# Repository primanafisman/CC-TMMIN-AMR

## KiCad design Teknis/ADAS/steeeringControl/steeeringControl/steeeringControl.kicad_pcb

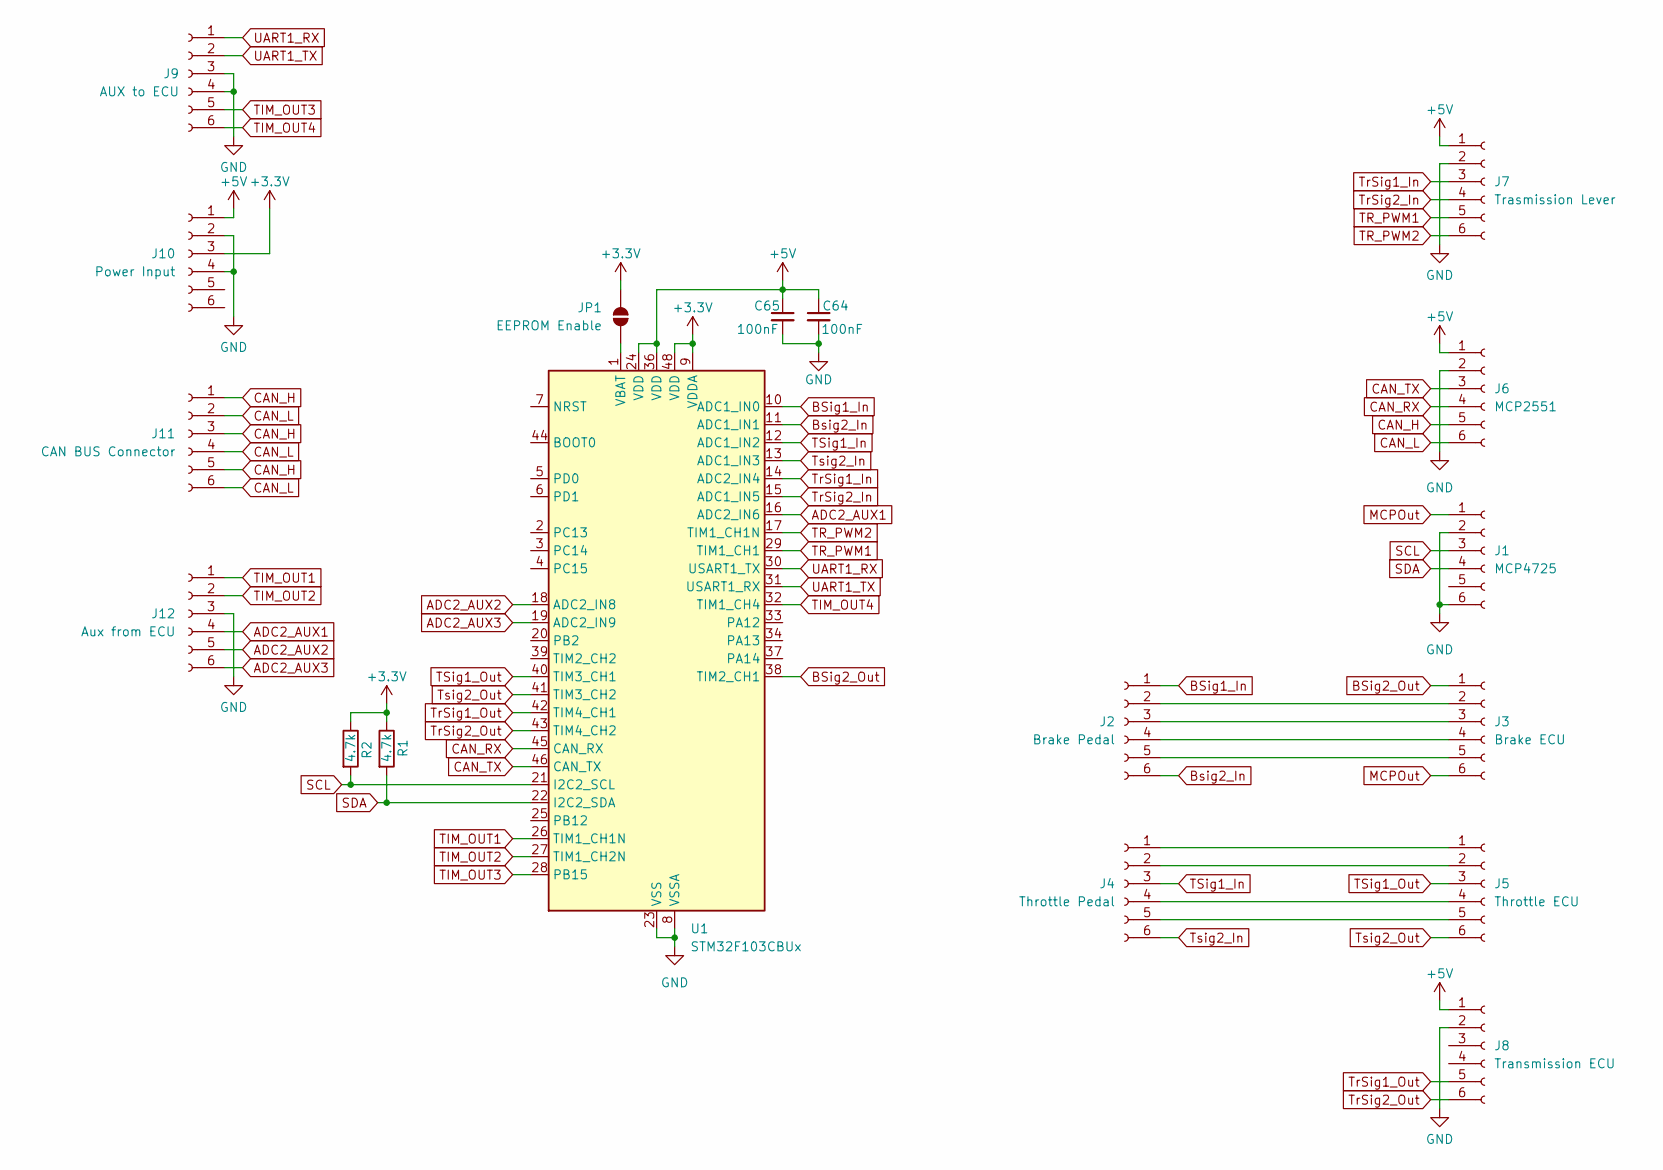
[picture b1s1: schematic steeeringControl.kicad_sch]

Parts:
C64, C65: 100nF; C_0805_2012Metric
J1: MCP4725; PinSocket_1x06_P2.54mm_Vertical
J2: Brake Pedal; JST_XH_S6B-XH-A-1_1x06_P2.50mm_Horizontal
J3: Brake ECU; JST_XH_S6B-XH-A-1_1x06_P2.50mm_Horizontal
J4: Throttle Pedal; JST_XH_S6B-XH-A-1_1x06_P2.50mm_Horizontal
J5: Throttle ECU; JST_XH_S6B-XH-A-1_1x06_P2.50mm_Horizontal
J6: MCP2551; PinSocket_1x06_P2.54mm_Vertical
J7: Trasmission Lever; JST_XH_S6B-XH-A-1_1x06_P2.50mm_Horizontal
J8: Transmission ECU; JST_XH_S6B-XH-A-1_1x06_P2.50mm_Horizontal
J9: AUX to ECU; JST_XH_S6B-XH-A-1_1x06_P2.50mm_Horizontal
J10: Power Input; JST_XH_S6B-XH-A-1_1x06_P2.50mm_Horizontal
J11: CAN BUS Connector; JST_XH_S6B-XH-A-1_1x06_P2.50mm_Horizontal
J12: Aux from ECU; JST_XH_S6B-XH-A-1_1x06_P2.50mm_Horizontal
JP1: EEPROM Enable; SolderJumper-2_P1.3mm_Open_RoundedPad1.0x1.5mm
R1, R2: 4.7k; R_0805_2012Metric
U1: STM32F103CBUx; STM32F103CBT6

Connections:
+3.3V: J10.3, JP1.1 (A), R1.1, R2.1, U1.9 (VDDA), U1.48 (VDD)
+5V: C64.1, C65.1, J6.1, J7.1, J8.1, J10.1, U1.24 (VDD), U1.36 (VDD)
ADC2_AUX1: J12.4, U1.16 (ADC2_IN6)
ADC2_AUX2: J12.5, U1.18 (ADC2_IN8)
ADC2_AUX3: J12.6, U1.19 (ADC2_IN9)
BSig1_In: J2.1, U1.10 (ADC1_IN0)
BSig2_Out: J3.1, U1.38 (TIM2_CH1)
Bsig2_In: J2.6, U1.11 (ADC1_IN1)
CAN_H: J6.5, J11.1, J11.3, J11.5
CAN_L: J6.6, J11.2, J11.4, J11.6
CAN_RX: J6.4, U1.45 (CAN_RX)
CAN_TX: J6.3, U1.46 (CAN_TX)
GND: C64.2, C65.2, J1.2, J1.6, J6.2, J7.2, J8.2, J9.3, J9.4, J10.2, J10.4, J12.3, U1.8 (VSSA), U1.23 (VSS), U1.35 (VSS), U1.47 (VSS), U1.49 (VSS)
MCPOut: J1.1, J3.6
unnamed: J2.2, J3.2
unnamed: J2.3, J3.3
unnamed: J2.4, J3.4
unnamed: J2.5, J3.5
unnamed: J4.1, J5.1
unnamed: J4.2, J5.2
unnamed: J4.4, J5.4
unnamed: J4.5, J5.5
unnamed: JP1.2 (B), U1.1 (VBAT)
SCL: J1.3, R2.2, U1.21 (I2C2_SCL)
SDA: J1.4, R1.2, U1.22 (I2C2_SDA)
TIM_OUT1: J12.1, U1.26 (TIM1_CH1N)
TIM_OUT2: J12.2, U1.27 (TIM1_CH2N)
TIM_OUT3: J9.5, U1.28 (PB15)
TIM_OUT4: J9.6, U1.32 (TIM1_CH4)
TR_PWM1: J7.5, U1.29 (TIM1_CH1)
TR_PWM2: J7.6, U1.17 (TIM1_CH1N)
TSig1_In: J4.3, U1.12 (ADC1_IN2)
TSig1_Out: J5.3, U1.40 (TIM3_CH1)
TrSig1_In: J7.3, U1.14 (ADC2_IN4)
TrSig1_Out: J8.5, U1.42 (TIM4_CH1)
TrSig2_In: J7.4, U1.15 (ADC1_IN5)
TrSig2_Out: J8.6, U1.43 (TIM4_CH2)
Tsig2_In: J4.6, U1.13 (ADC1_IN3)
Tsig2_Out: J5.6, U1.41 (TIM3_CH2)
UART1_RX: J9.1, U1.30 (USART1_TX)
UART1_TX: J9.2, U1.31 (USART1_RX)

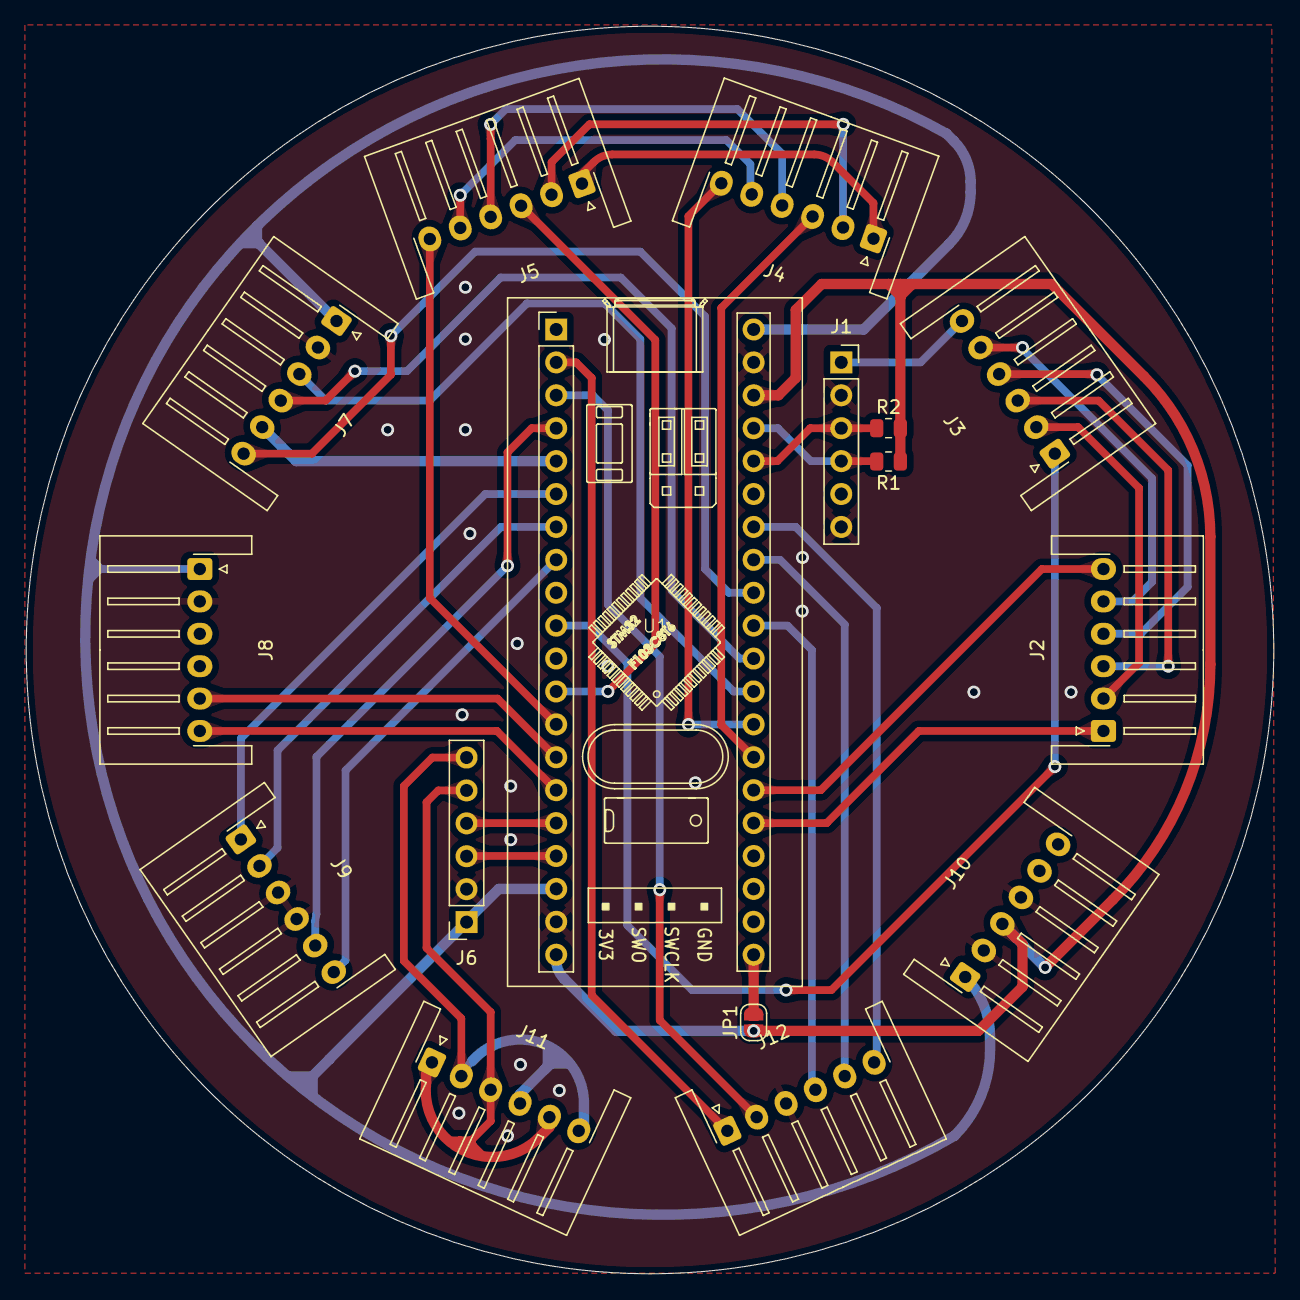
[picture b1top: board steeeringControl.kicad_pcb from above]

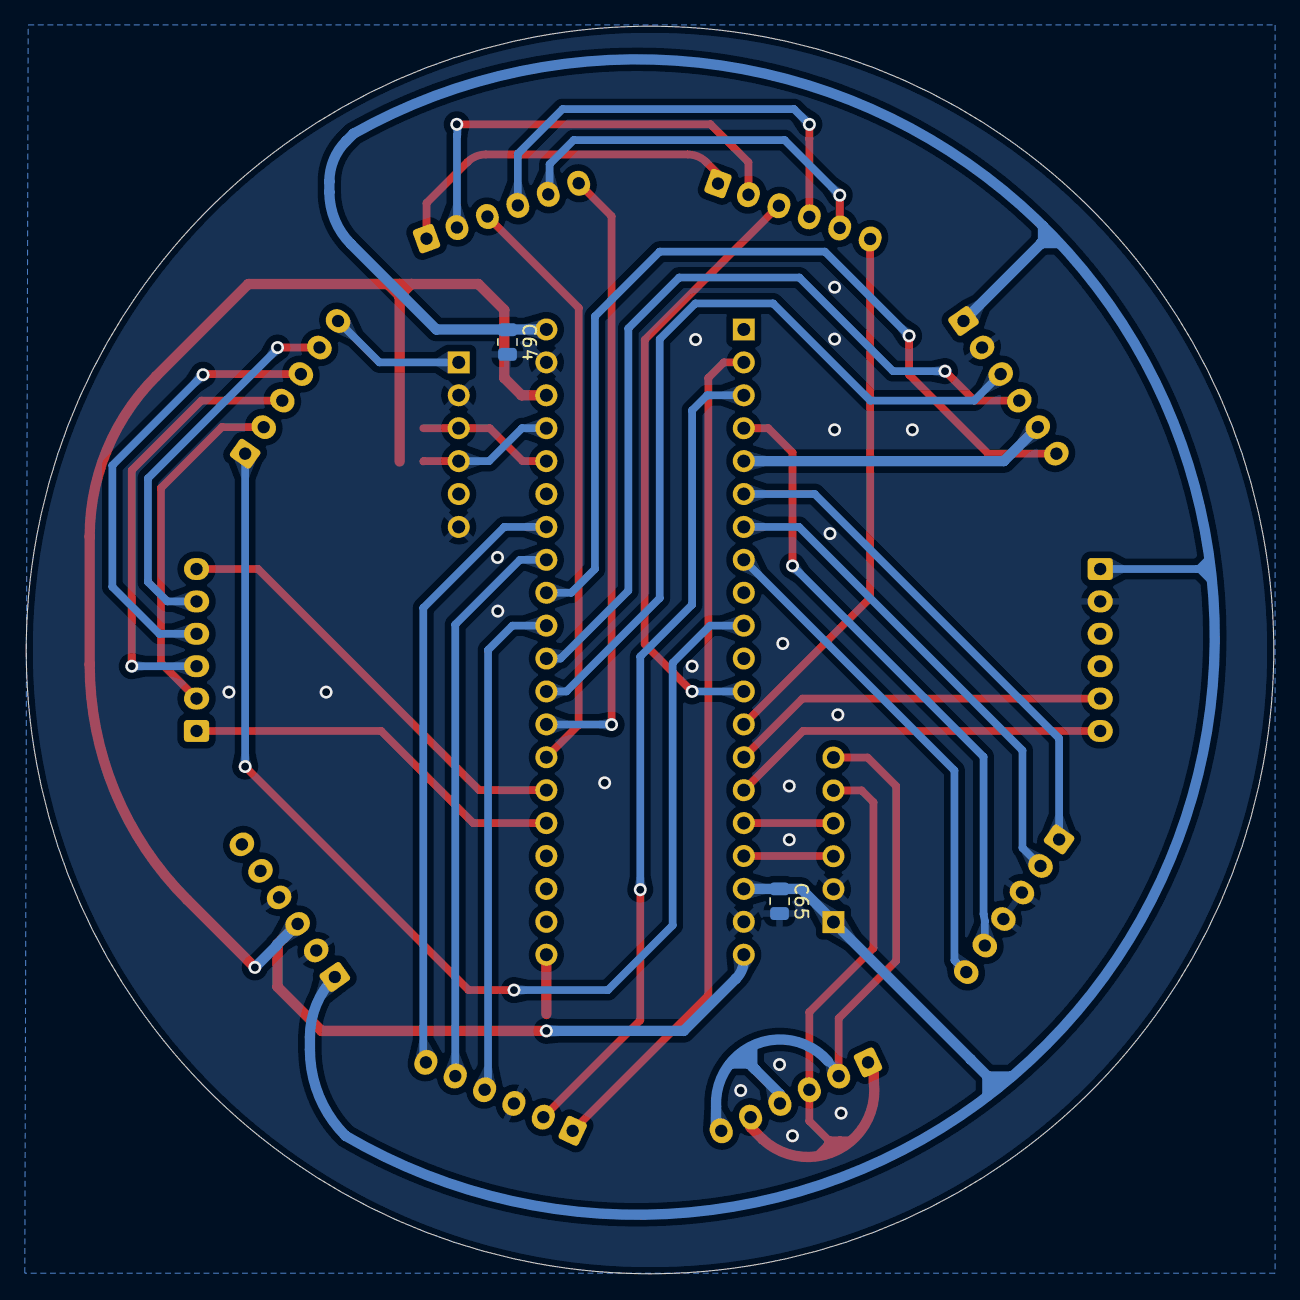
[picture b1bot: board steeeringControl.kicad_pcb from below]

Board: 2 copper layers, 96.3 x 96.3 mm, 18 parts (2 on the bottom side), 41 nets.

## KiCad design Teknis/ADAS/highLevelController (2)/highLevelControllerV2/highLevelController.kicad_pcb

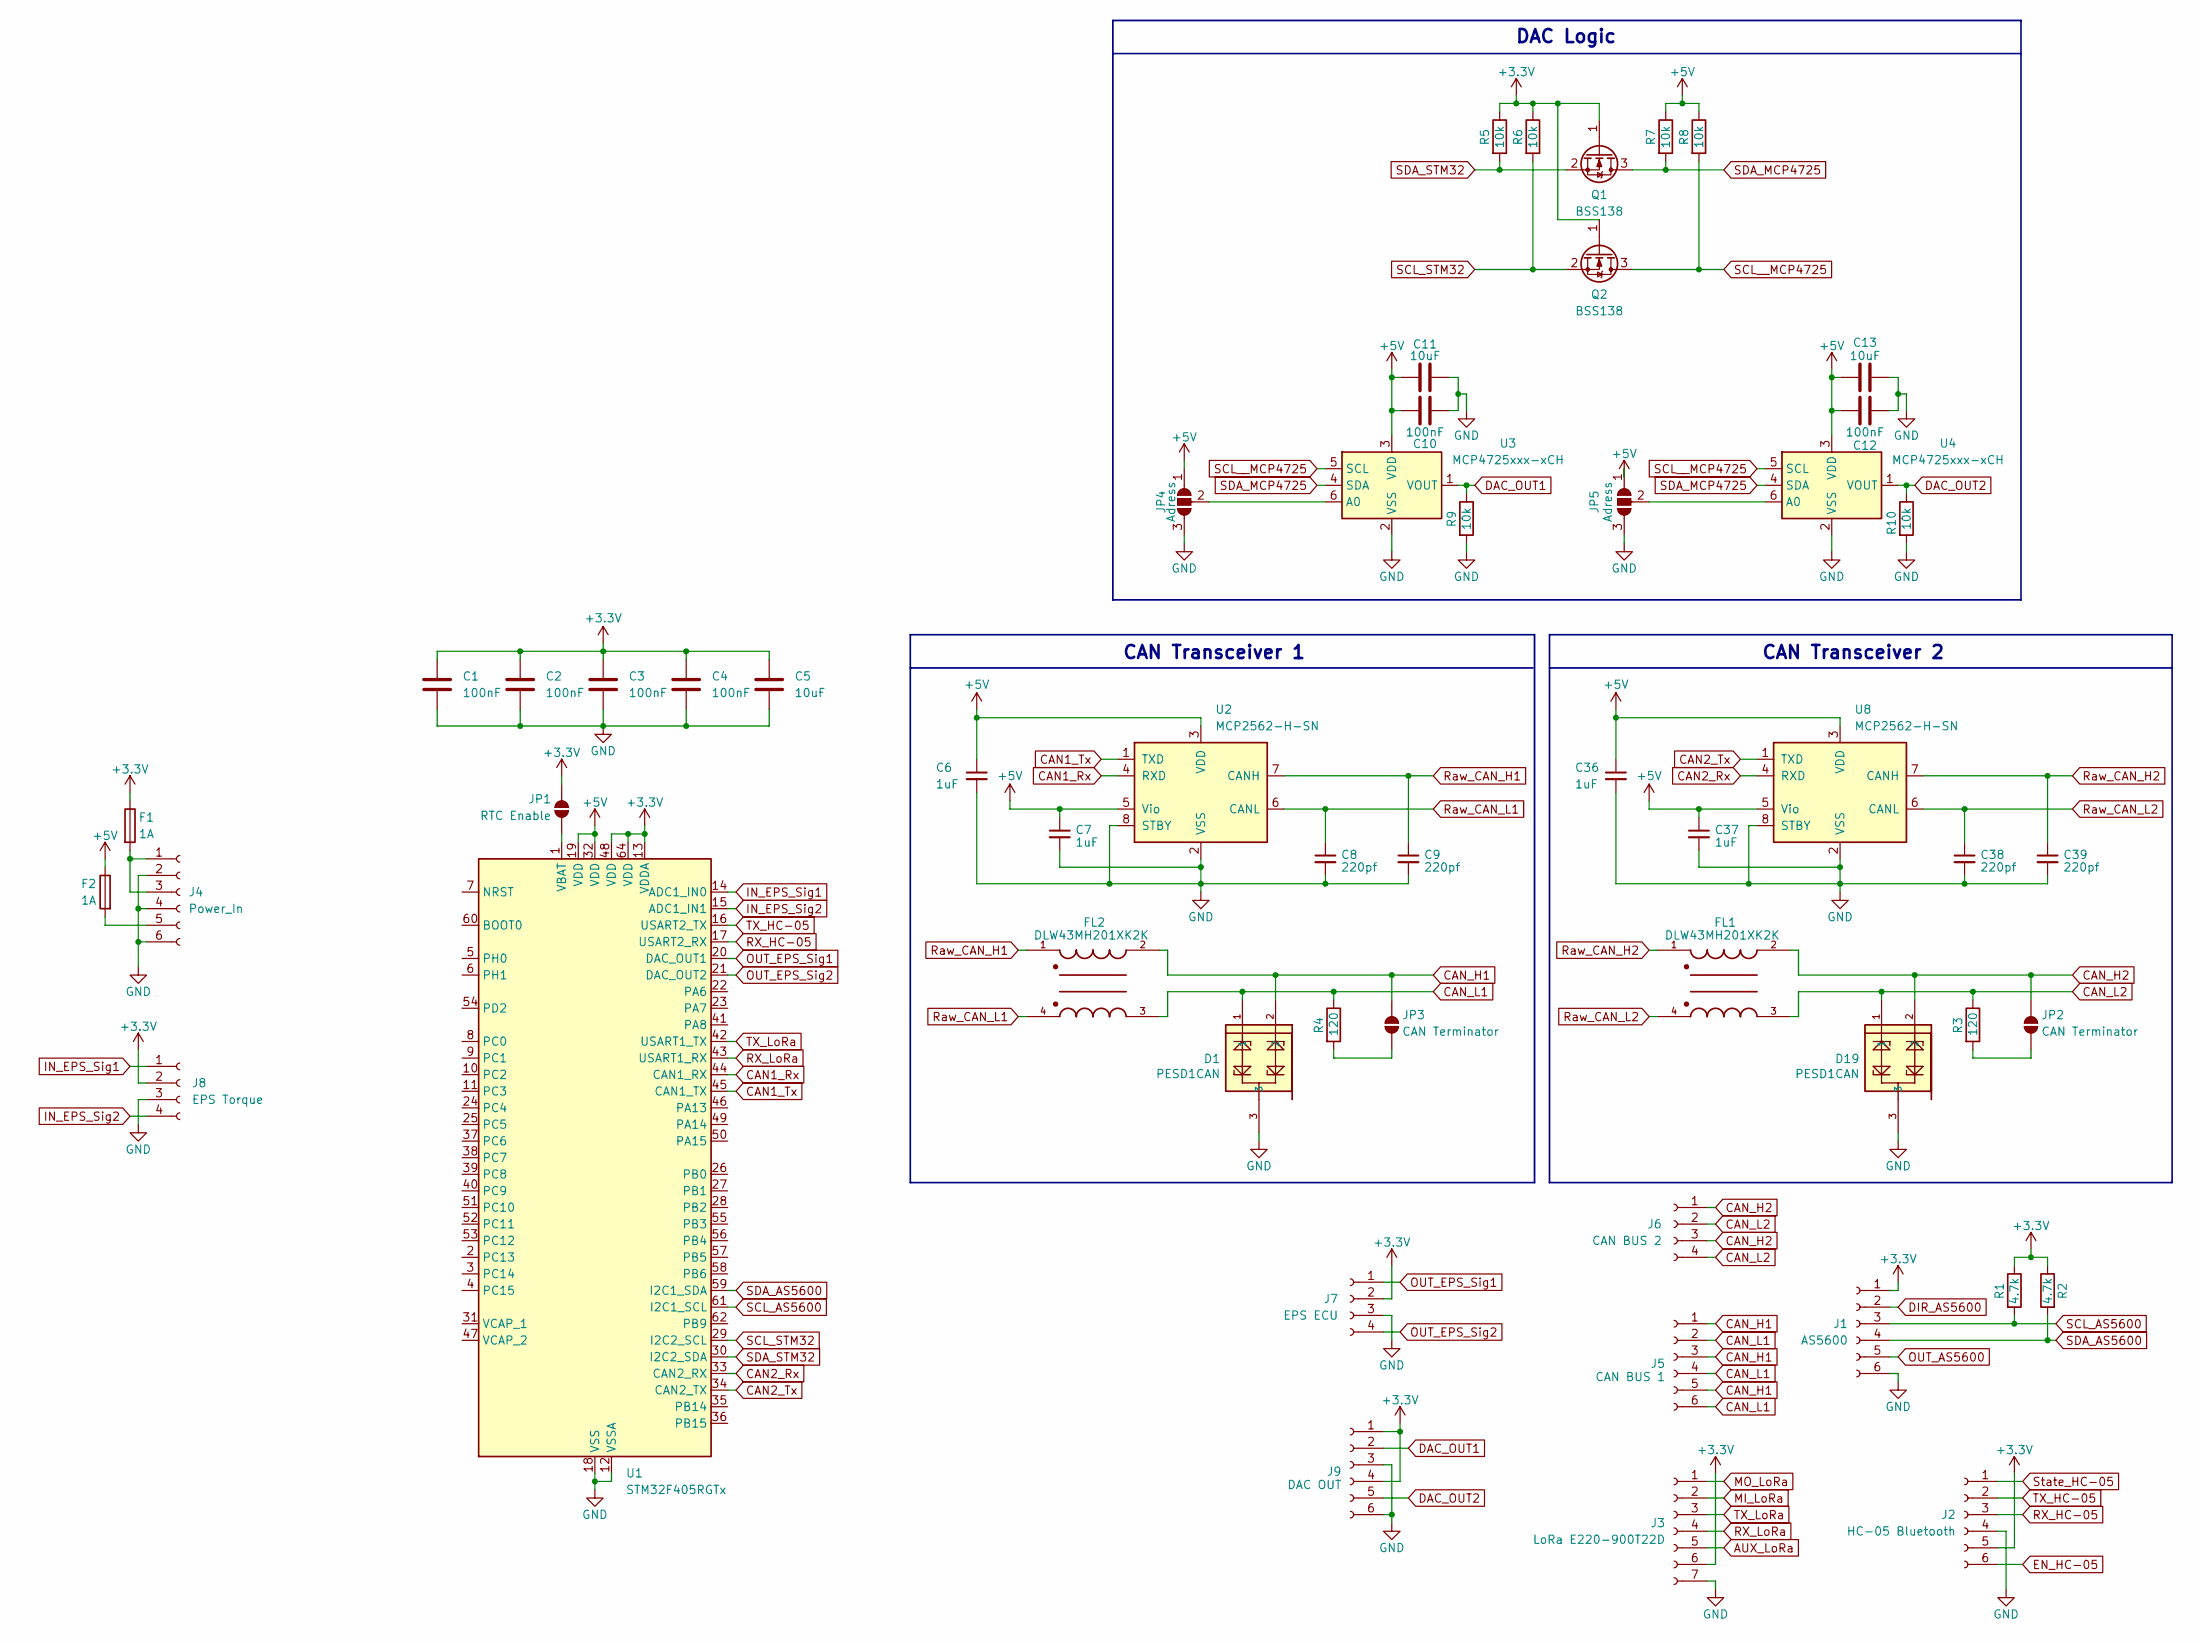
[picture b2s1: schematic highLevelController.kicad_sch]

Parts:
C1, C2, C3, C4, C10, C12: 100nF; C_0603_1608Metric
C5, C11, C13: 10uF; C_0603_1608Metric
C6, C7, C36, C37: 1uF; C_0603_1608Metric
C8, C9, C38, C39: 220pf; C_0603_1608Metric
D1, D19: PESD1CAN; SOT-23
F1, F2: 1A; Fuse_1206_3216Metric
FL1, FL2: DLW43MH201XK2K; DLW43; PARTREV N/A
J1: AS5600; JST_XH_S6B-XH-A-1_1x06_P2.50mm_Horizontal
J2: HC-05 Bluetooth; PinSocket_1x06_P2.54mm_Vertical
J3: LoRa E220-900T22D; PinSocket_1x07_P2.54mm_Vertical
J4: Power_In; JST_XH_S6B-XH-A-1_1x06_P2.50mm_Horizontal
J5: CAN BUS 1; JST_XH_S6B-XH-A-1_1x06_P2.50mm_Horizontal
J6: CAN BUS 2; JST_XH_S4B-XH-A-1_1x04_P2.50mm_Horizontal
J7: EPS ECU; JST_XH_S4B-XH-A-1_1x04_P2.50mm_Horizontal
J8: EPS Torque; JST_XH_S4B-XH-A-1_1x04_P2.50mm_Horizontal
J9: DAC OUT; JST_XH_S6B-XH-A-1_1x06_P2.50mm_Horizontal
JP1: RTC Enable; SolderJumper-2_P1.3mm_Open_TrianglePad1.0x1.5mm
JP2, JP3: CAN Terminator; SolderJumper-2_P1.3mm_Open_TrianglePad1.0x1.5mm
JP4, JP5: Adress; SolderJumper-3_P2.0mm_Open_TrianglePad1.0x1.5mm_NumberLabels
Q1, Q2: BSS138; SOT-23
R1, R2: 4.7k; R_0603_1608Metric
R3, R4: 120; R_0603_1608Metric
R5, R6, R7, R8, R9, R10: 10k; R_0603_1608Metric
U1: STM32F405RGTx; STM32F405RGT6
U2, U8: MCP2562-H-SN; SOIC-8_3.9x4.9mm_P1.27mm
U3, U4: MCP4725xxx-xCH; SOT-23-6

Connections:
+3.3V: C1.1, C2.1, C3.1, C4.1, C5.1, F1.1, J1.1, J2.5, J3.6, J7.2, J8.2, J9.1, J9.4, JP1.1 (A), Q1.1 (G), Q2.1 (G), R1.1, R2.1, R5.1, R6.1, U1.13 (VDDA), U1.48 (VDD), U1.64 (VDD)
+5V: C6.1, C7.1, C10.1, C11.1, C12.1, C13.1, C36.1, C37.1, F2.1, JP4.1 (A), JP5.1 (A), R7.1, R8.1, U1.19 (VDD), U1.32 (VDD), U2.3 (VDD), U2.5 (Vio), U3.3 (VDD), U4.3 (VDD), U8.3 (VDD), U8.5 (Vio)
AUX_LoRa: J3.5
CAN1_Rx: U1.44 (CAN1_RX), U2.4 (RXD)
CAN1_Tx: U1.45 (CAN1_TX), U2.1 (TXD)
CAN2_Rx: U1.33 (CAN2_RX), U8.4 (RXD)
CAN2_Tx: U1.34 (CAN2_TX), U8.1 (TXD)
CAN_H1: D1.2, FL2.2, J5.1, J5.3, J5.5, JP3.1 (A)
CAN_H2: D19.2, FL1.2, J6.1, J6.3, JP2.1 (A)
CAN_L1: D1.1, FL2.3, J5.2, J5.4, J5.6, R4.1
CAN_L2: D19.1, FL1.3, J6.2, J6.4, R3.1
DAC_OUT1: J9.2, R9.1, U3.1 (VOUT)
DAC_OUT2: J9.5, R10.1, U4.1 (VOUT)
DIR_AS5600: J1.2
EN_HC-05: J2.6
GND: C1.2, C2.2, C3.2, C4.2, C5.2, C6.2, C7.2, C8.2, C9.2, C10.2, C11.2, C12.2, C13.2, C36.2, C37.2, C38.2, C39.2, D1.3, D19.3, J1.6, J2.4, J3.7, J4.2, J4.4, J4.6, J7.3, J8.3, J9.3, J9.6, JP4.3 (B), JP5.3 (B), R9.2, R10.2, U1.12 (VSSA), U1.18 (VSS), U1.63 (VSS), U2.2 (VSS), U2.8 (STBY), U3.2 (VSS), U4.2 (VSS), U8.2 (VSS), U8.8 (STBY)
IN_EPS_Sig1: J8.1, U1.14 (ADC1_IN0)
IN_EPS_Sig2: J8.4, U1.15 (ADC1_IN1)
MI_LoRa: J3.2
MO_LoRa: J3.1
unnamed: F1.2, J4.1, J4.3
unnamed: F2.2, J4.5
unnamed: JP1.2 (B), U1.1 (VBAT)
unnamed: JP2.2 (B), R3.2
unnamed: JP3.2 (B), R4.2
unnamed: JP4.2 (C), U3.6 (A0)
unnamed: JP5.2 (C), U4.6 (A0)
OUT_AS5600: J1.5
OUT_EPS_Sig1: J7.1, U1.20 (DAC_OUT1)
OUT_EPS_Sig2: J7.4, U1.21 (DAC_OUT2)
RX_HC-05: J2.3, U1.17 (USART2_RX)
RX_LoRa: J3.4, U1.43 (USART1_RX)
Raw_CAN_H1: C9.1, FL2.1, U2.7 (CANH)
Raw_CAN_H2: C39.1, FL1.1, U8.7 (CANH)
Raw_CAN_L1: C8.1, FL2.4, U2.6 (CANL)
Raw_CAN_L2: C38.1, FL1.4, U8.6 (CANL)
SCL_AS5600: J1.3, R1.2, U1.61 (I2C1_SCL)
SCL_STM32: Q2.2 (S), R6.2, U1.29 (I2C2_SCL)
SCL__MCP4725: Q2.3 (D), R8.2, U3.5 (SCL), U4.5 (SCL)
SDA_AS5600: J1.4, R2.2, U1.59 (I2C1_SDA)
SDA_MCP4725: Q1.3 (D), R7.2, U3.4 (SDA), U4.4 (SDA)
SDA_STM32: Q1.2 (S), R5.2, U1.30 (I2C2_SDA)
State_HC-05: J2.1
TX_HC-05: J2.2, U1.16 (USART2_TX)
TX_LoRa: J3.3, U1.42 (USART1_TX)

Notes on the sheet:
CAN Transceiver 1
CAN Transceiver 2
DAC Logic

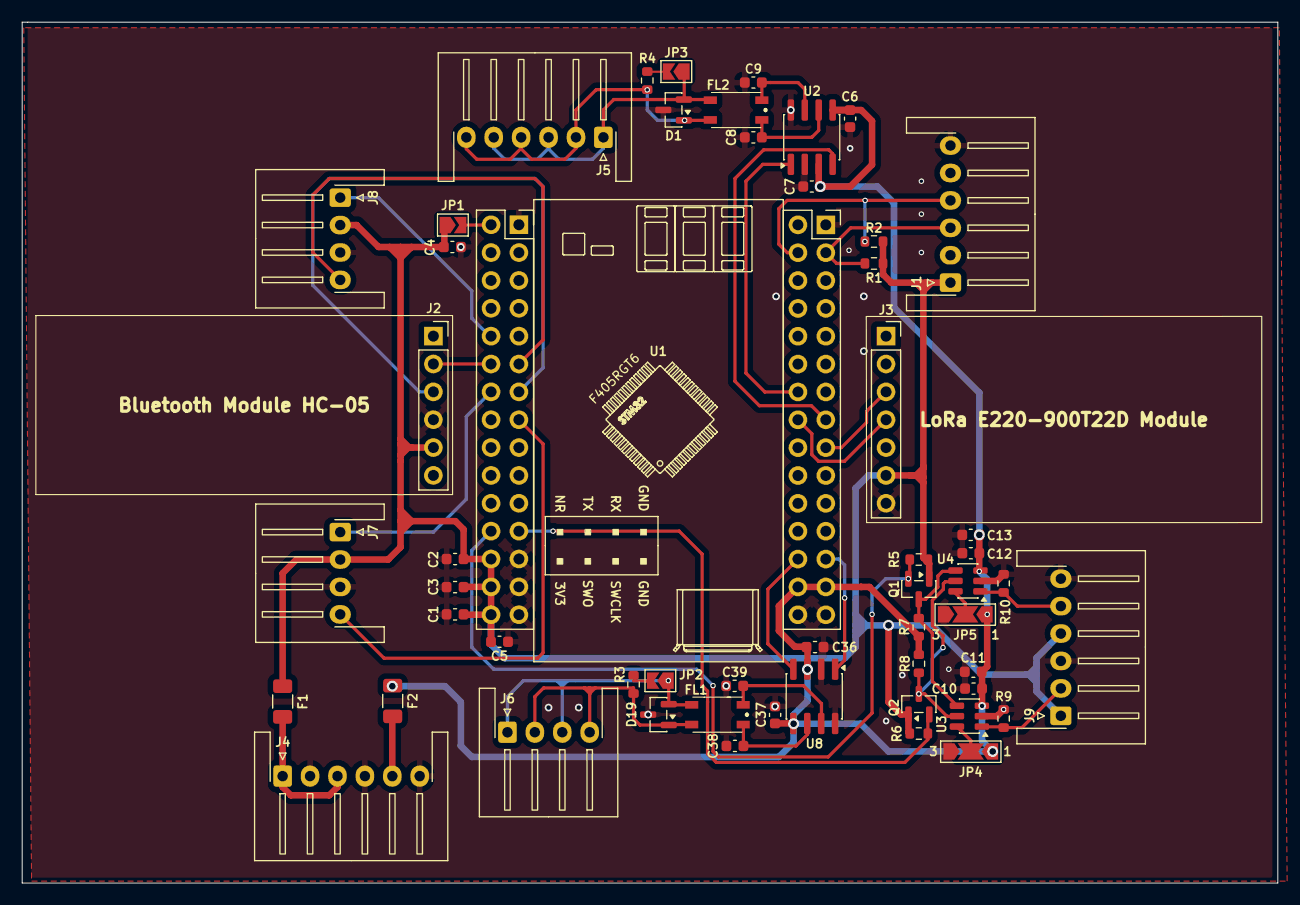
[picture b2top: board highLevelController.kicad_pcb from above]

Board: 2 copper layers, 114.5 x 78.5 mm, 54 parts (0 on the bottom side), 38 nets.

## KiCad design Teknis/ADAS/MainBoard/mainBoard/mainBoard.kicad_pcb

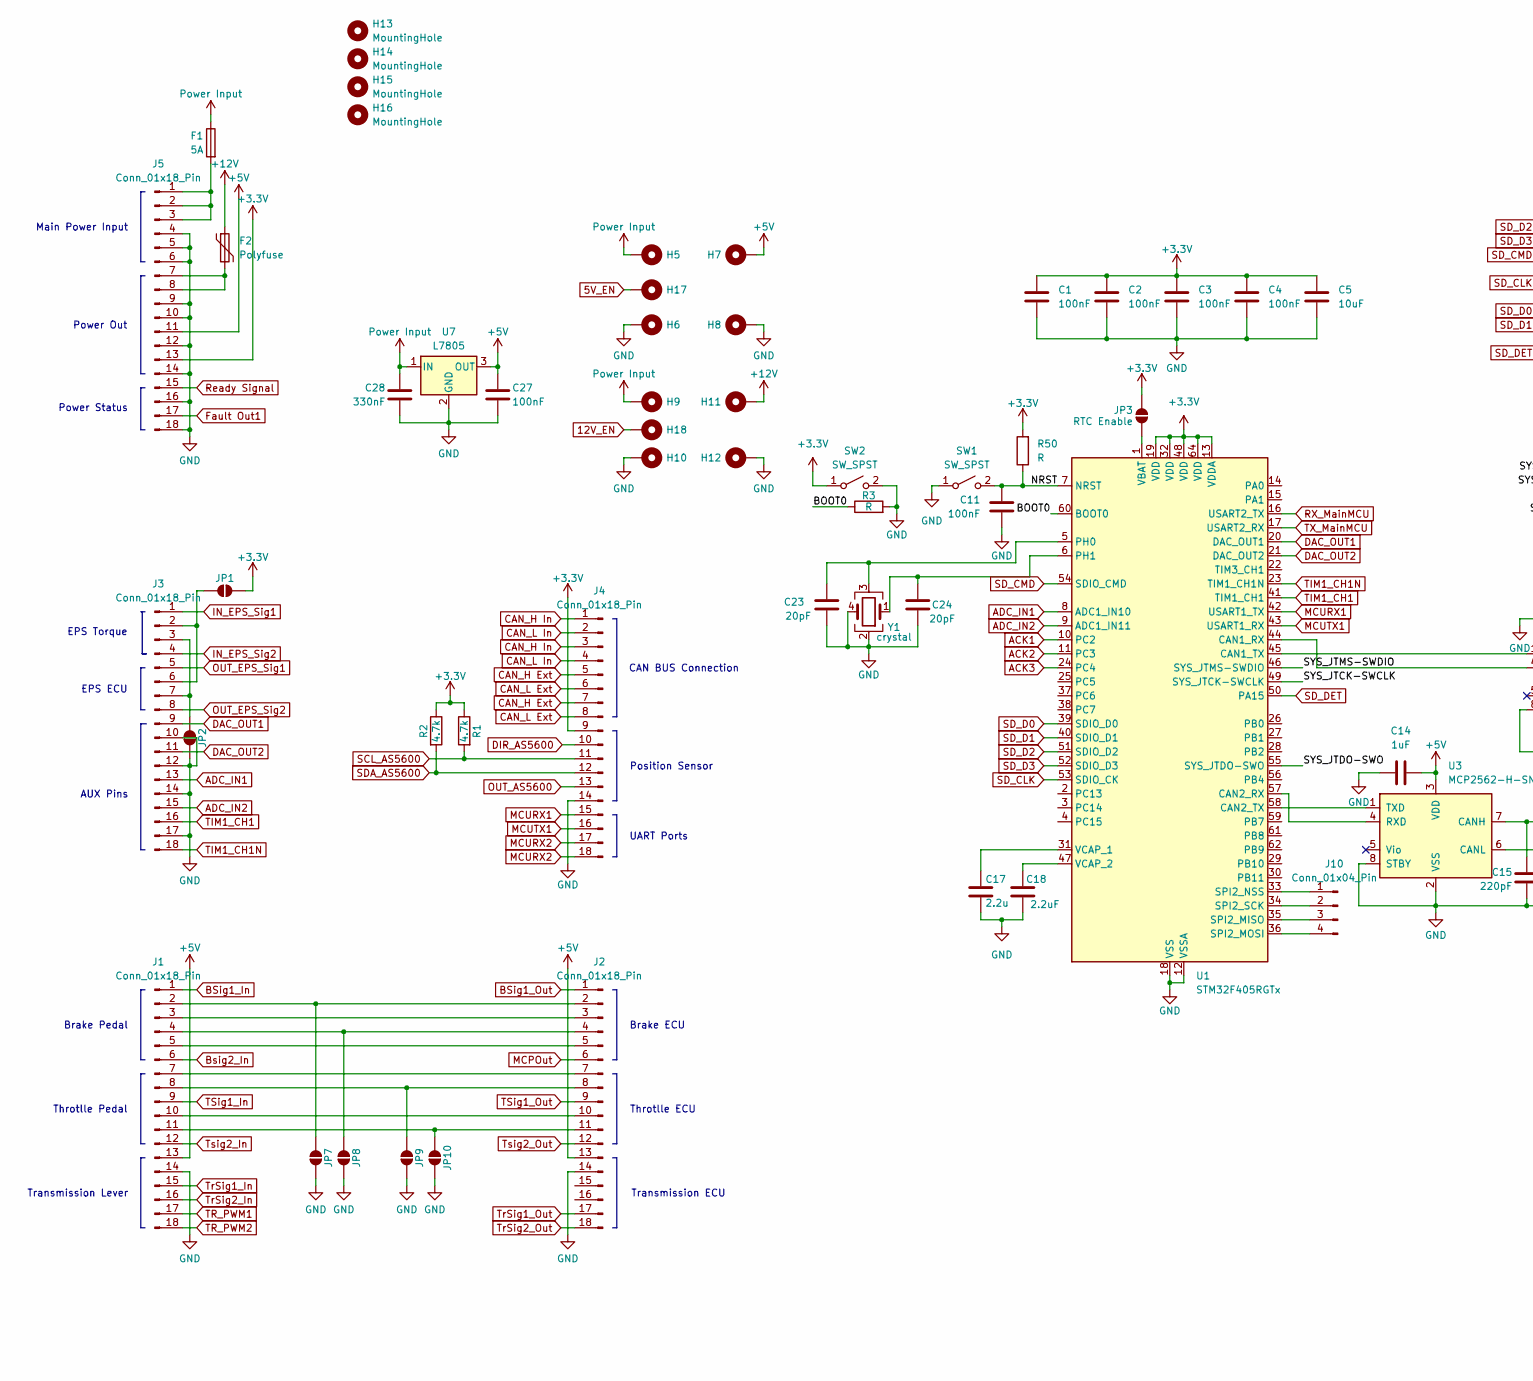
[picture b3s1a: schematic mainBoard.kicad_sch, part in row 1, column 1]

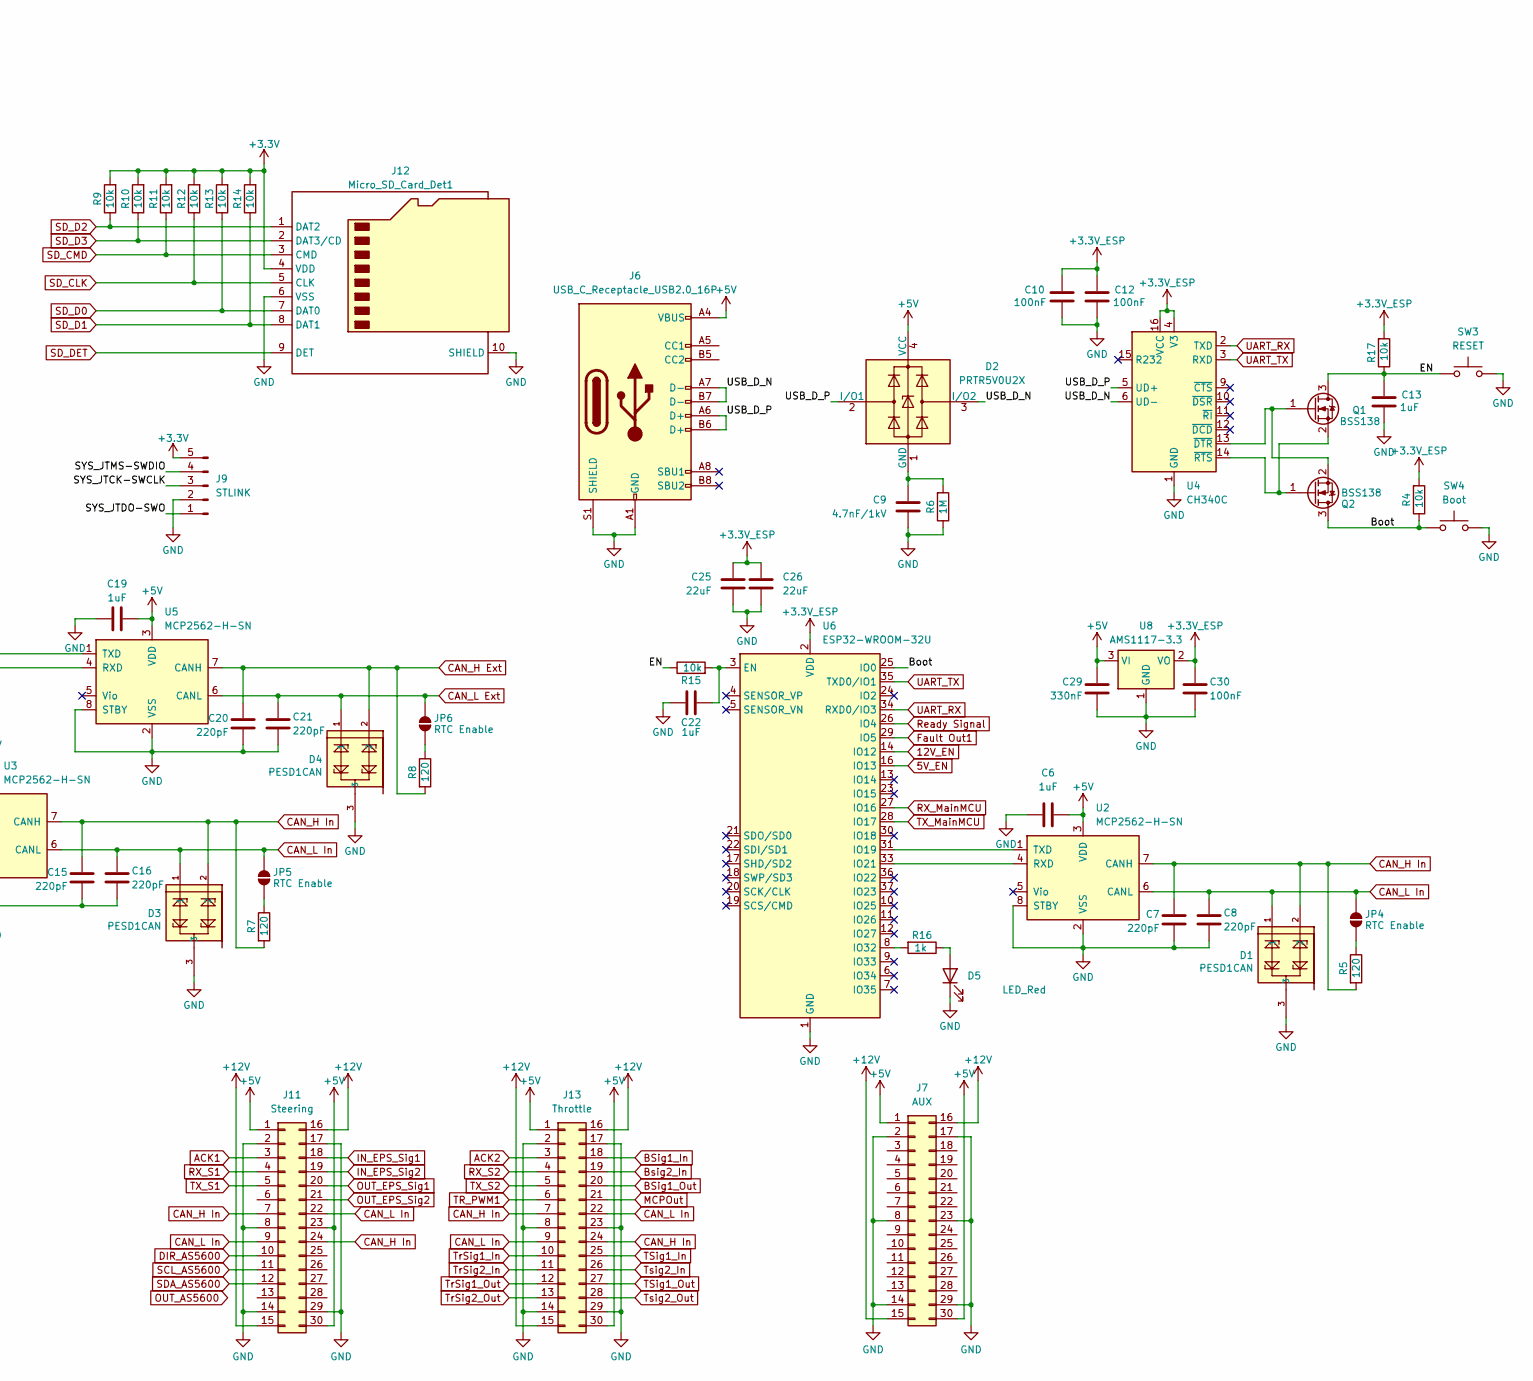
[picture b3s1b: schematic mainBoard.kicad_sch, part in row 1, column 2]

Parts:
C1, C2, C3, C4, C11: 100nF; C_0402_1005Metric_Pad0.74x0.62mm_HandSolder
C5: 10uF; C_0402_1005Metric_Pad0.74x0.62mm_HandSolder
C6, C14, C19, C22: 1uF; C_0805_2012Metric
C7, C8, C15, C16, C20, C21: 220pF; C_0805_2012Metric
C9: 4.7nF/1kV; C_0805_2012Metric
C10, C12: 100nF; C_1206_3216Metric
C13: 1uF; C_1206_3216Metric
C17: 2.2u; C_0402_1005Metric_Pad0.74x0.62mm_HandSolder
C18: 2.2uF; C_0402_1005Metric_Pad0.74x0.62mm_HandSolder
C23, C24: 20pF; C_0402_1005Metric_Pad0.74x0.62mm_HandSolder
C25, C26: 22uF; C_0805_2012Metric
C27, C30: 100nF; C_0805_2012Metric
C28, C29: 330nF; C_0805_2012Metric
D1, D3, D4: PESD1CAN; SOT-23
D2: PRTR5V0U2X; SOT-143
D5: LED_Red; LED_0805_2012Metric
F1: 5A; Fuse_1206_3216Metric
F2: Polyfuse; Fuse_1812_4532Metric
H5, H6, H7, H8, H9, H10, H11, H12, H17, H18: MountingHole_Pad; SolderWirePad_1x01_SMD_5x10mm
H13, H14, H15, H16: MountingHole; MountingHole_3.2mm_M3
J1, J2, J3, J4, J5: Conn_01x18_Pin; JAE_MX23A18NF1
J6: USB_C_Receptacle_USB2.0_16P; USB_C_Receptacle_GCT_USB4110
J7: AUX; Jamma30pin-Male
J9: STLINK; PinSocket_1x05_P2.54mm_Vertical
J10: Conn_01x04_Pin; JST_XH_B4B-XH-A_1x04_P2.50mm_Vertical
J11: Steering; Jamma30pin-Male
J12: Micro_SD_Card_Det1; J_SD_Card-micro_socket_A
J13: Throttle; Jamma30pin-Male
JP1, JP2, JP7, JP8, JP9, JP10: SolderJumper_2_Open; SolderJumper-2_P1.3mm_Open_TrianglePad1.0x1.5mm
JP3, JP4, JP5, JP6: RTC Enable; SolderJumper-2_P1.3mm_Open_TrianglePad1.0x1.5mm
Q1, Q2: BSS138; SOT-23
R1, R2: 4.7k; R_0603_1608Metric
R3, R50: R; R_0402_1005Metric_Pad0.72x0.64mm_HandSolder
R4, R15, R17: 10k; R_0805_2012Metric
R5, R7, R8: 120; R_0805_2012Metric
R6: 1M; R_0805_2012Metric
R9, R10, R11, R12, R13, R14: 10k; R_0402_1005Metric_Pad0.72x0.64mm_HandSolder
R16: 1k; R_0805_2012Metric
SW1, SW2: SW_SPST; SW_SPST_PTS810
SW3: RESET; SW_SPST_CK_RS282G05A3
SW4: Boot; SW_SPST_CK_RS282G05A3
U1: STM32F405RGTx; LQFP-64_10x10mm_P0.5mm
U2, U3, U5: MCP2562-H-SN; SOIC-8_3.9x4.9mm_P1.27mm
U4: CH340C; SOIC-16_3.9x9.9mm_P1.27mm
U6: ESP32-WROOM-32U
U7: L7805; TO-252-2
U8: AMS1117-3.3; SOT-223-3_TabPin2
Y1: crystal; Crystal_SMD_3225-4Pin_3.2x2.5mm

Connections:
5V_EN: H17.1, U6.16 (IO13)
12V_EN: H18.1, U6.14 (IO12)
+3.3V: C1.1, C2.1, C3.1, C4.1, C5.1, J4.9, J5.13, J9.5, J12.4 (VDD), JP1.1 (A), JP3.1 (A), R1.1, R2.1, R9.2, R10.2, R11.2, R12.2, R13.2, R14.2, R50.2, SW2.1 (A), U1.13 (VDDA), U1.19 (VDD), U1.32 (VDD), U1.48 (VDD), U1.64 (VDD)
+3.3V_ESP: C10.1, C12.1, C25.1, C26.1, C30.1, R4.2, R17.2, U4.4 (V3), U4.16 (VCC), U6.2 (VDD), U8.2 (VO)
+5V: C6.2, C14.2, C19.2, C27.1, C29.1, D2.4 (VCC), H7.1, J1.13, J2.13, J5.11, J6.A4 (VBUS), J6.A9 (VBUS), J6.B4 (VBUS), J6.B9 (VBUS), J7.1, J7.30, J11.1, J11.23, J11.30, J13.1, J13.30, U2.3 (VDD), U3.3 (VDD), U5.3 (VDD), U7.3 (OUT), U8.3 (VI)
+12V: F2.1, H11.1, J7.15, J7.16, J11.15, J11.16, J13.15, J13.16
/BOOT0: R3.1, U1.60 (BOOT0)
/Boot: Q2.3 (D), R4.1, SW4.2, U6.25 (IO0)
/EN: C13.1, Q1.3 (D), R15.1, R17.1, SW3.2
/NRST: C11.1, R50.1, SW1.2 (B), U1.7 (NRST)
/SYS_JTCK-SWCLK: J9.3, U1.49 (SYS_JTCK-SWCLK)
/SYS_JTDO-SWO: J9.1, U1.55 (SYS_JTDO-SWO)
/SYS_JTMS-SWDIO: J9.4, U1.46 (SYS_JTMS-SWDIO)
/USB_D_N: D2.3 (I/O2), J6.A7 (D-), J6.B7 (D-), U4.6 (UD-)
/USB_D_P: D2.2 (I/O1), J6.A6 (D+), J6.B6 (D+), U4.5 (UD+)
ACK1: J11.3, U1.10 (PC2)
ACK2: J13.3, U1.11 (PC3)
ACK3: U1.24 (PC4)
ADC_IN1: J3.13, U1.8 (ADC1_IN10)
ADC_IN2: J3.15, U1.9 (ADC1_IN11)
BSig1_In: J1.1, J13.18
BSig1_Out: J2.1, J13.20
Bsig2_In: J1.6, J13.19
CAN_H Ext: C20.1, D4.2, J4.5, J4.7, R8.2, U5.7 (CANH)
CAN_H In: C7.1, C15.1, D1.2, D3.2, J4.1, J4.3, J11.7, J11.24, J13.7, J13.24, R5.2, R7.2, U2.7 (CANH), U3.7 (CANH)
CAN_L Ext: C21.1, D4.1, J4.6, J4.8, JP6.1 (A), U5.6 (CANL)
CAN_L In: C8.1, C16.1, D1.1, D3.1, J4.2, J4.4, J11.9, J11.22, J13.9, J13.22, JP4.1 (A), JP5.1 (A), U2.6 (CANL), U3.6 (CANL)
DAC_OUT1: J3.9, U1.20 (DAC_OUT1)
DAC_OUT2: J3.11, U1.21 (DAC_OUT2)
DIR_AS5600: J4.10, J11.10
Fault Out1: J5.17, U6.29 (IO5)
GND: C1.2, C2.2, C3.2, C4.2, C5.2, C6.1, C7.2, C8.2, C9.2, C10.2, C11.2, C12.2, C13.2, C14.1, C15.2, C16.2, C17.1, C18.1, C19.1, C20.2, C21.2, C22.1, C23.2, C24.2, C25.2, C26.2, C27.2, C28.2, C29.2, C30.2, D1.3, D3.3, D4.3, D5.1 (K), H6.1, H8.1, H10.1, H12.1, J1.14, J2.14, J3.10, J3.12, J3.14, J3.17, J4.14, J5.4, J5.5, J5.6, J5.9, J5.10, J5.12, J5.14, J5.16, J5.18, J6.A1 (GND), J6.A12 (GND), J6.B1 (GND), J6.B12 (GND), J6.S1 (SHIELD), J7.2, J7.8, J7.14, J7.17, J7.23, J7.29, J9.2, J11.2, J11.8, J11.14, J11.17, J11.29, J12.6 (VSS), J12.10 (SHIELD), J13.2, J13.8, J13.14, J13.17, J13.23, J13.29, JP2.1 (A), JP7.1 (A), JP8.1 (A), JP9.1 (A), JP10.1 (A), R3.2, R6.1, SW1.1 (A), SW2.2 (B), SW3.1, SW4.1, U1.12 (VSSA), U1.18 (VSS), U1.63 (VSS), U2.2 (VSS), U2.8 (STBY), U3.2 (VSS), U3.8 (STBY), U4.1 (GND), U5.2 (VSS), U5.8 (STBY), U6.1 (GND), U6.15 (GND), U6.38 (GND), U6.39 (GND), U7.2 (GND), U8.1 (GND), Y1.2, Y1.4
IN_EPS_Sig1: J3.1, J11.18
IN_EPS_Sig2: J3.4, J11.19
MCPOut: J2.6, J13.21
MCURX1: J4.15, U1.42 (USART1_TX)
MCURX2: J4.17, J4.18
MCUTX1: J4.16, U1.43 (USART1_RX)
unnamed: C9.1, D2.1 (GND), R6.2
unnamed: D5.2 (A), R16.1
unnamed: J1.2, J2.2, JP7.2 (B)
unnamed: J1.3, J2.3
unnamed: J1.4, J2.4, JP8.2 (B)
unnamed: J1.5, J2.5
unnamed: J1.7, J2.7
unnamed: J1.8, J2.8, JP9.2 (B)
unnamed: J1.10, J2.10
unnamed: J1.11, J2.11, JP10.2 (B)
unnamed: J3.2, J3.6, JP1.2 (B)
unnamed: J3.3, J3.7, JP2.2 (B)
unnamed: F1.2, J5.1, J5.2, J5.3
unnamed: F2.2, J5.7, J5.8
unnamed: J10.1, U1.33 (SPI2_NSS)
unnamed: J10.2, U1.34 (SPI2_SCK)
unnamed: J10.3, U1.35 (SPI2_MISO)
unnamed: J10.4, U1.36 (SPI2_MOSI)
unnamed: JP3.2 (B), U1.1 (VBAT)
unnamed: JP4.2 (B), R5.1
unnamed: JP5.2 (B), R7.1
unnamed: JP6.2 (B), R8.1
unnamed: Q1.1 (G), Q2.2 (S), U4.13 (~DTR)
unnamed: Q1.2 (S), Q2.1 (G), U4.14 (~RTS)
unnamed: U1.44 (CAN1_RX), U5.4 (RXD)
unnamed: U1.45 (CAN1_TX), U5.1 (TXD)
unnamed: U1.57 (CAN2_RX), U3.4 (RXD)
unnamed: U1.58 (CAN2_TX), U3.1 (TXD)
unnamed: C23.1, U1.5 (PH0), Y1.3
unnamed: C24.1, U1.6 (PH1), Y1.1
unnamed: C17.2, U1.31 (VCAP_1)
unnamed: C18.2, U1.47 (VCAP_2)
unnamed: U2.4 (RXD), U6.33 (IO21)
unnamed: U2.1 (TXD), U6.31 (IO19)
unnamed: C22.2, R15.2, U6.3 (EN)
unnamed: R16.2, U6.8 (IO32)
OUT_AS5600: J4.13
OUT_EPS_Sig1: J3.5, J11.20
OUT_EPS_Sig2: J3.8, J11.21
Power Input: C28.1, F1.1, H5.1, H9.1, U7.1 (IN)
RX_MainMCU: U1.16 (USART2_TX), U6.27 (IO16)
RX_S1: J11.4
RX_S2: J13.4
Ready Signal: J5.15, U6.26 (IO4)
SCL_AS5600: J4.11, J11.11, R1.2
SDA_AS5600: J4.12, J11.12, R2.2
SD_CLK: J12.5 (CLK), R12.1, U1.53 (SDIO_CK)
SD_CMD: J12.3 (CMD), R11.1, U1.54 (SDIO_CMD)
SD_D0: J12.7 (DAT0), R13.1, U1.39 (SDIO_D0)
SD_D1: J12.8 (DAT1), R14.1, U1.40 (SDIO_D1)
SD_D2: J12.1 (DAT2), R9.1, U1.51 (SDIO_D2)
SD_D3: J12.2 (DAT3/CD), R10.1, U1.52 (SDIO_D3)
SD_DET: J12.9 (DET), U1.50 (PA15)
TIM1_CH1: J3.16, U1.41 (TIM1_CH1)
TIM1_CH1N: J3.18, U1.23 (TIM1_CH1N)
TR_PWM1: J1.17, J13.6
TR_PWM2: J1.18
TSig1_In: J1.9, J13.25
TSig1_Out: J2.9, J13.27
TX_MainMCU: U1.17 (USART2_RX), U6.28 (IO17)
TX_S1: J11.5
TX_S2: J13.5
TrSig1_In: J1.15, J13.10
TrSig1_Out: J2.17, J13.12
TrSig2_In: J1.16, J13.11
TrSig2_Out: J2.18, J13.13
Tsig2_In: J1.12, J13.26
Tsig2_Out: J2.12, J13.28
UART_RX: U4.2 (TXD), U6.34 (RXD0/IO3)
UART_TX: U4.3 (RXD), U6.35 (TXD0/IO1)

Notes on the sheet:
Transmission Lever
Brake ECU
AUX Pins
Power Out
UART Ports
Throtlle Pedal
EPS ECU
Transmission ECU
Power Status
EPS Torque
Position Sensor
CAN BUS Connection
Brake Pedal
Throtlle ECU
Main Power Input

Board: 2 copper layers, 106 parts (0 on the bottom side), 101 nets, no tracks yet.

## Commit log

2026-04-08 First upload for TMMIN project
